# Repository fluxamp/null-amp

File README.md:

## About

This repository contains the layout for a battery-powered differential amplifier with a small input range. It is intended to be used in a nullmeter setup.

Feel free to copy, modify and redistribute the schematic and layout.

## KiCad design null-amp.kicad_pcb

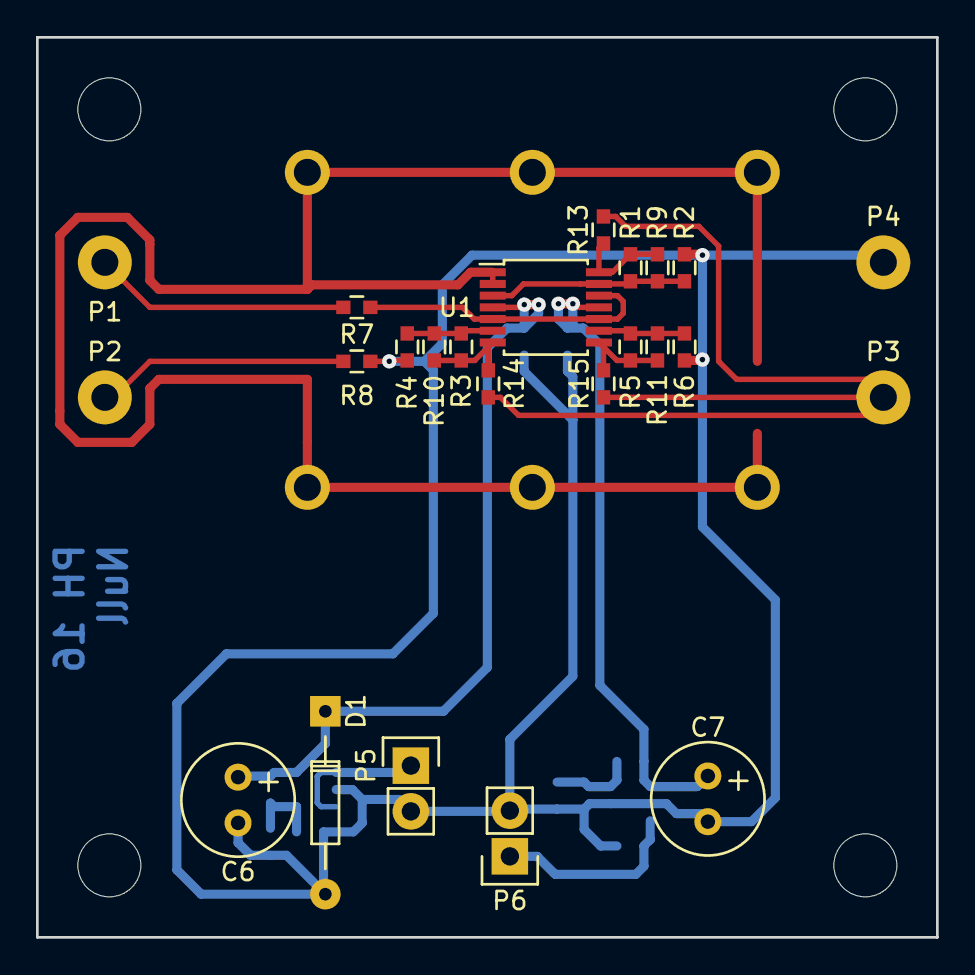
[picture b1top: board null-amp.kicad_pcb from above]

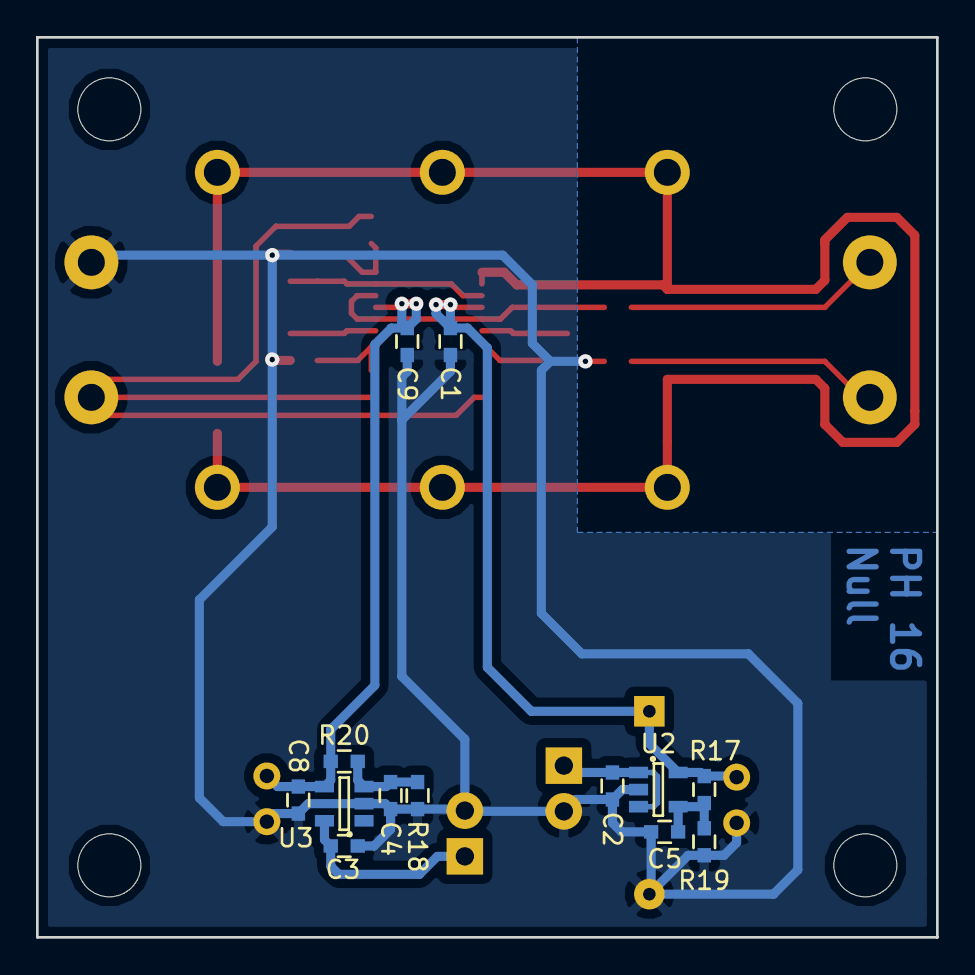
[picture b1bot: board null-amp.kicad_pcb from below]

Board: 2 copper layers, 50.0 x 50.0 mm, 43 parts (13 on the bottom side), 18 nets.

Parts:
2mm_hole, 2mm_hole#2, 2mm_hole#3, 2mm_hole#4, 2mm_hole#5, 2mm_hole#6: VAL**; 2mm_hole
C1, C9: 0.1u; C_0603
C2, C3, C8: 1u; C_0603
C4, C5: 470p; C_0603
C6, C7: 4.7u; Elko_vert_11.2x6.3mm_RM2.5_CopperClear
D1: D; Diode_DO-35_SOD27_Horizontal_RM10
P1: REF1; Measurement_Point_Round-TH_Big
P2: REF2; Measurement_Point_Round-TH_Big
P3: OUTPUT; Measurement_Point_Round-TH_Big
P4: OUT_GND; Measurement_Point_Round-TH_Big
P5, P6: CONN_01X02; Pin_Header_Straight_1x02
R1, R3, R5: 180k; C_0603
R2, R4, R6: 1k; C_0603
R7, R8: 27R; C_0603
R9, R10, R11: 220k; C_0603
R13, R14, R15: 10R; C_0603
R17, R18, R19: 10k; C_0603
R20: 10.7k; C_0603
U1: IC-Hq; TSSOP-14_4.4x5mm_Pitch0.65mm
U2: MIC5205; SOT-23-5
U3: MIC5270; SOT-23-5

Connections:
+2V5: C1.1, C6.1, D1.1, R17.2, U1.4, U2.5
GND: C1.2, C2.2, C3.2, C4.1, C5.2, C6.2, C7.2, C8.2, C9.1, D1.2, P4.1, P5.2, P6.2, R2.2, R4.2, R6.2, R8.1, R18.2, R19.2, U2.2, U3.2
unnamed: C2.1, P5.1, U2.1, U2.3
unnamed: C3.1, P6.1, U3.5
unnamed: C4.2, R18.1, R20.2, U3.3
unnamed: C5.1, R17.1, R19.1, U2.4
unnamed: P1.1, R7.2
unnamed: P2.1, R8.2
unnamed: P3.1, R13.1, R14.1, R15.1
unnamed: R1.1, R9.1, R13.2, U1.14
unnamed: R1.2, R2.1, R9.2, U1.3, U1.13
unnamed: R7.1, U1.5, U1.10, U1.12
unnamed: R3.1, R10.1, R14.2, U1.7
unnamed: R3.2, R4.1, R10.2, U1.6
unnamed: R5.1, R11.1, R15.2, U1.8
unnamed: R5.2, R6.1, R11.2, U1.9
SHIELD: 2mm_hole.1, 2mm_hole#2.1, 2mm_hole#3.1, 2mm_hole#4.1, 2mm_hole#5.1, 2mm_hole#6.1, U1.1, U1.2
VSS: C7.1, C8.1, C9.2, R20.1, U1.11, U3.4

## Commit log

2017-11-12 layout and schematic
2017-11-12 added picture
